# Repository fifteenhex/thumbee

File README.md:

This is dead. Look at https://github.com/fifteenhex/breadbee instead. It actually works. :D

# thumbee
MStar MSC313E SoC breakout

#rev0

Rough layout. Minimal decoupling caps because of limited space. Test to see if two layers works.
May move to some 0402 passives if not.

## bugs

Pinout foobar #1. USB ground isn't wired up because of a difference in the pin number of the symbol
and the footprint. Fixed by shorting the id pin to ground next to it.

Pinout foobar #2. avdd_nodie and dvdd_nodie are swapped. *edit* Maybe not. Seems like there is a datasheet
mistake. Pinout in the pin diagram is correct *edit* 

Pinout foobar #3. spi mosi and spi miso are swapped

Holtek USB->Serial chip is a piece of shit and can't handle lower baud rate data before data at the 
baud read the port was opened with.

1.8v supply is no good. The chip is very sensitive to the 1.8v rail dropping slightly (probably because
the DDR gets corrupted when it happens). On boot up the 1.8v drops for a split second and this makes
bootup hit or miss. Removing the 3.3va ldo and wiring 3.3va to 3.3v allows the input voltage to be lowered
to ~3.5v from the intended 5v and that makes the drop smaller.

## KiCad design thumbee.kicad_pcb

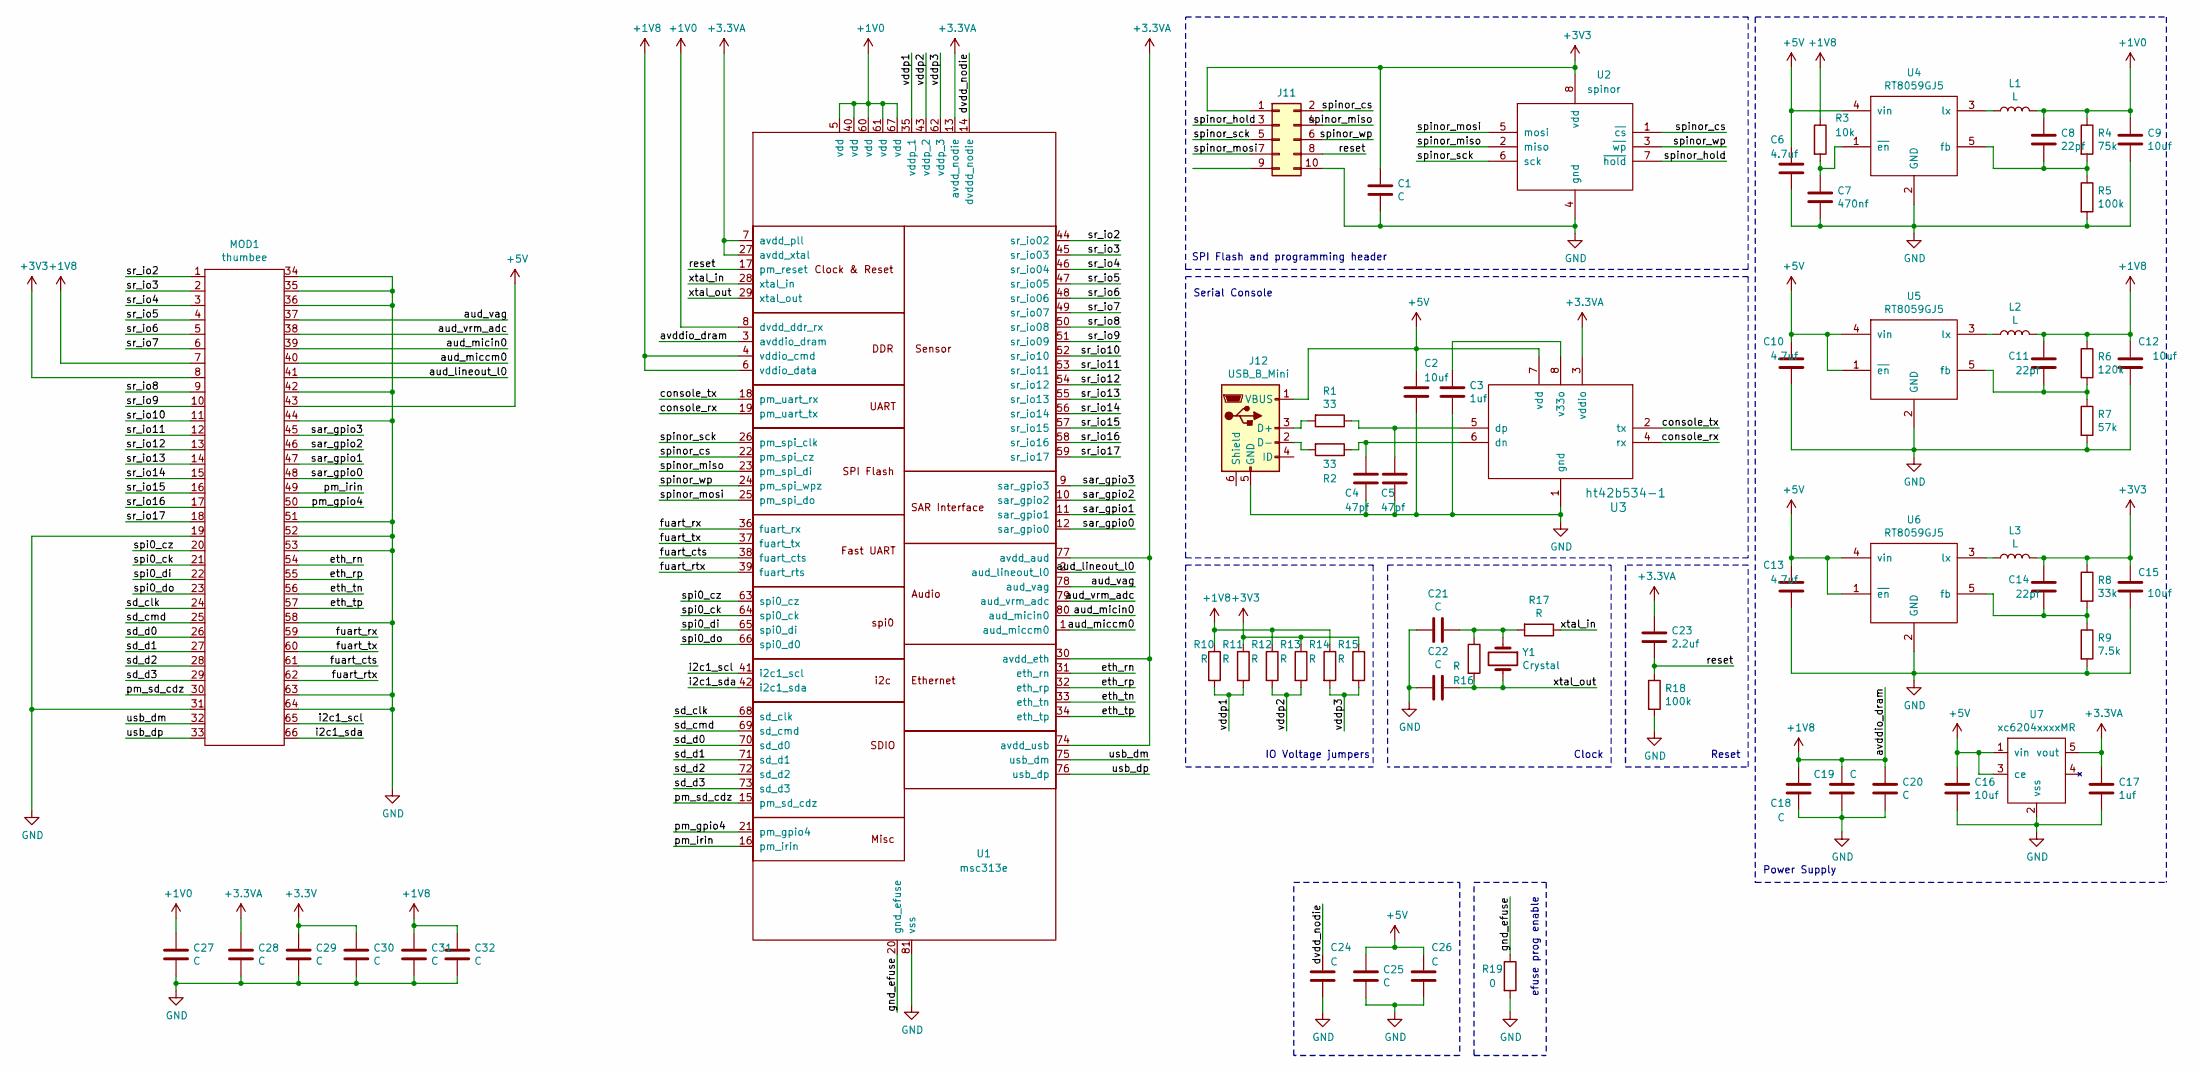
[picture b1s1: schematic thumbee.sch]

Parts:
C1, C18, C19, C20, C21, C22, C24, C25, C26, C27, C28, C29, C30, C31, C32: C; C_0603_1608Metric
C2, C9, C12, C15, C16: 10uf; C_0603_1608Metric
C3, C17: 1uf; C_0603_1608Metric
C4, C5: 47pf; C_0603_1608Metric
C6, C10, C13: 4.7uf; C_0603_1608Metric
C7: 470nf; C_0603_1608Metric
C8, C11, C14: 22pf; C_0603_1608Metric
C23: 2.2uf; C_0603_1608Metric
J11: Conn_02x05_Odd_Even; PinHeader_2x05_P1.00mm_Vertical_SMD
J12: USB_B_Mini; USB-MICRO-B
L1, L2, L3: L; CD32
MOD1: thumbee
R1, R2: 33; R_0603_1608Metric
R3: 10k; R_0603_1608Metric
R4: 75k; R_0603_1608Metric
R5, R18: 100k; R_0603_1608Metric
R6: 120k; R_0603_1608Metric
R7: 57k; R_0603_1608Metric
R8: 33k; R_0603_1608Metric
R9: 7.5k; R_0603_1608Metric
R10, R11, R12, R13, R14, R15, R16, R17: R; R_0603_1608Metric
R19: 0; R_0603_1608Metric
U1: msc313e; QFN-80_EP_8x8_Pitch0.35mm
U2: spinor; wson8-8x6mm
U3: ht42b534-1; SOIC-8_3.9x4.9mm_P1.27mm
U4, U5, U6: RT8059GJ5; TSOT-23-5
U7: xc6204xxxxMR; TSOT-23-5
Y1: Crystal; Crystal_SMD_5032-2Pin_5.0x3.2mm

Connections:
+1V0: C8.1, C9.1, C27.1, L1.2, R4.1, U1.5 (vdd), U1.8 (dvdd_ddr_rx), U1.40 (vdd), U1.60 (vdd), U1.61 (vdd), U1.67 (vdd)
+1V8: C11.1, C12.1, C18.1, C19.1, C20.1, C31.1, C32.1, L2.2, MOD1.7, R3.1, R6.1, R10.1, R12.1, R14.1, U1.3 (avddio_dram), U1.4 (vddio_cmd), U1.6 (vddio_data)
+3.3VA: C17.1, C23.1, C28.1, U1.7 (avdd_pll), U1.13 (avdd_nodie), U1.27 (avdd_xtal), U1.30 (avdd_eth), U1.74 (avdd_usb), U1.77 (avdd_aud), U3.3 (vddio), U7.5 (vout)
+5V: C2.1, C6.1, C10.1, C13.1, C16.1, C25.1, C26.1, J12.1 (VBUS), MOD1.43, U3.7 (vdd), U4.4 (vin), U5.1 (~en), U5.4 (vin), U6.1 (~en), U6.4 (vin), U7.1 (vin), U7.3 (ce)
/aud_lineout_l0: MOD1.41, U1.2 (aud_lineout_l0)
/aud_miccm0: MOD1.40, U1.1 (aud_miccm0)
/aud_micin0: MOD1.39, U1.80 (aud_micin0)
/aud_vag: MOD1.37, U1.78 (aud_vag)
/aud_vrm_adc: MOD1.38, U1.79 (aud_vrm_adc)
/console_rx: U1.19 (pm_uart_tx), U3.4 (rx)
/console_tx: U1.18 (pm_uart_rx), U3.2 (tx)
/dvdd_nodie: C24.2, U1.14 (dvddd_nodie)
/eth_rn: MOD1.54, U1.31 (eth_rn)
/eth_rp: MOD1.55, U1.32 (eth_rp)
/eth_tn: MOD1.56, U1.33 (eth_tn)
/eth_tp: MOD1.57, U1.34 (eth_tp)
/fuart_cts: MOD1.61, U1.38 (fuart_cts)
/fuart_rtx: MOD1.62, U1.39 (fuart_rts)
/fuart_rx: MOD1.59, U1.36 (fuart_rx)
/fuart_tx: MOD1.60, U1.37 (fuart_tx)
/gnd_efuse: R19.1, U1.20 (gnd_efuse)
/i2c1_scl: MOD1.65, U1.41 (i2c1_scl)
/i2c1_sda: MOD1.66, U1.42 (i2c1_sda)
/pm_gpio4: MOD1.50, U1.21 (pm_gpio4)
/pm_irin: MOD1.49, U1.16 (pm_irin)
/pm_sd_cdz: MOD1.30, U1.15 (pm_sd_cdz)
/reset: C23.2, J11.8, R18.1, U1.17 (pm_reset)
/sar_gpio0: MOD1.48, U1.12 (sar_gpio0)
/sar_gpio1: MOD1.47, U1.11 (sar_gpio1)
/sar_gpio2: MOD1.46, U1.10 (sar_gpio2)
/sar_gpio3: MOD1.45, U1.9 (sar_gpio3)
/sd_clk: MOD1.24, U1.68 (sd_clk)
/sd_cmd: MOD1.25, U1.69 (sd_cmd)
/sd_d0: MOD1.26, U1.70 (sd_d0)
/sd_d1: MOD1.27, U1.71 (sd_d1)
/sd_d2: MOD1.28, U1.72 (sd_d2)
/sd_d3: MOD1.29, U1.73 (sd_d3)
/spi0_ck: MOD1.21, U1.64 (spi0_ck)
/spi0_cz: MOD1.20, U1.63 (spi0_cz)
/spi0_di: MOD1.22, U1.65 (spi0_di)
/spi0_do: MOD1.23, U1.66 (spi0_d0)
/spinor_cs: J11.2, U1.22 (pm_spi_cz), U2.1 (~cs)
/spinor_hold: J11.3, U2.7 (~hold)
/spinor_miso: J11.4, U1.23 (pm_spi_di), U2.2 (miso)
/spinor_mosi: J11.7, U1.25 (pm_spi_do), U2.5 (mosi)
/spinor_sck: J11.5, U1.26 (pm_spi_clk), U2.6 (sck)
/spinor_wp: J11.6, U1.24 (pm_spi_wpz), U2.3 (~wp)
/sr_io2: MOD1.1, U1.44 (sr_io02)
/sr_io3: MOD1.2, U1.45 (sr_io03)
/sr_io4: MOD1.3, U1.46 (sr_io04)
/sr_io5: MOD1.4, U1.47 (sr_io05)
/sr_io6: MOD1.5, U1.48 (sr_io06)
/sr_io7: MOD1.6, U1.49 (sr_io07)
/sr_io8: MOD1.9, U1.50 (sr_io08)
/sr_io9: MOD1.10, U1.51 (sr_io09)
/sr_io10: MOD1.11, U1.52 (sr_io10)
/sr_io11: MOD1.12, U1.53 (sr_io11)
/sr_io12: MOD1.13, U1.54 (sr_io12)
/sr_io13: MOD1.14, U1.55 (sr_io13)
/sr_io14: MOD1.15, U1.56 (sr_io14)
/sr_io15: MOD1.16, U1.57 (sr_io15)
/sr_io16: MOD1.17, U1.58 (sr_io16)
/sr_io17: MOD1.18, U1.59 (sr_io17)
/usb_dm: MOD1.32, U1.75 (usb_dm)
/usb_dp: MOD1.33, U1.76 (usb_dp)
/vddp1: R10.2, R11.2, U1.35 (vddp_1)
/vddp2: R12.2, R13.2, U1.43 (vddp_2)
/vddp3: R14.2, R15.2, U1.62 (vddp_3)
/xtal_in: R17.1, U1.28 (xtal_in)
/xtal_out: C22.2, R16.2, U1.29 (xtal_out), Y1.2
GND: C1.2, C2.2, C3.2, C4.2, C5.2, C6.2, C7.2, C9.2, C10.2, C12.2, C13.2, C15.2, C16.2, C17.2, C18.2, C19.2, C20.2, C21.2, C22.1, C24.1, C25.2, C26.2, C27.2, C28.2, C29.2, C30.2, C31.2, C32.2, J11.10, J12.5 (GND), MOD1.19, MOD1.31, MOD1.34, MOD1.35, MOD1.36, MOD1.42, MOD1.44, MOD1.51, MOD1.52, MOD1.53, MOD1.58, MOD1.63, MOD1.64, R5.2, R7.2, R9.2, R18.2, R19.2, U1.81 (vss), U2.4 (gnd), U3.1 (gnd), U4.2 (GND), U5.2 (GND), U6.2 (GND), U7.2 (vss)
unnamed: C3.1, U3.8 (v33o)
unnamed: C4.1, R2.1, U3.6 (dn)
unnamed: C5.1, R1.1, U3.5 (dp)
unnamed: C7.1, R3.2, U4.1 (~en)
unnamed: C8.2, R4.2, R5.1, U4.5 (fb)
unnamed: C11.2, R6.2, R7.1, U5.5 (fb)
unnamed: C14.2, R8.2, R9.1, U6.5 (fb)
unnamed: C21.1, R16.1, R17.2, Y1.1
unnamed: J12.2 (D-), R2.2
unnamed: J12.3 (D+), R1.2
unnamed: L1.1, U4.3 (lx)
unnamed: L2.1, U5.3 (lx)
unnamed: L3.1, U6.3 (lx)

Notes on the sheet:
Power Supply
Reset
Serial Console
Clock
IO Voltage jumpers
efuse prog enable
SPI Flash and programming header

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
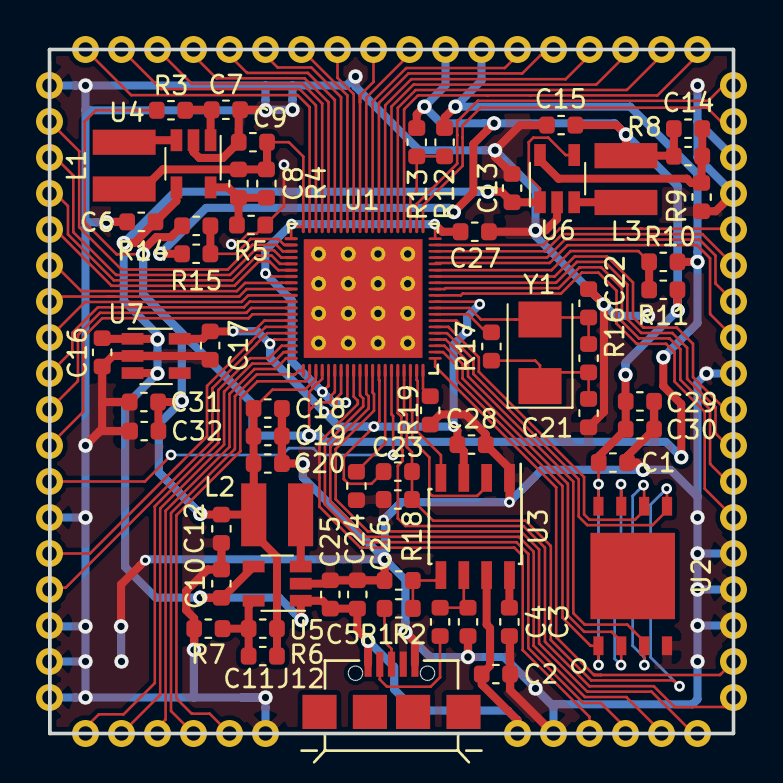
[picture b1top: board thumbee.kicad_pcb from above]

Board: 2 copper layers, 38.0 x 38.0 mm, 65 parts (1 on the bottom side), 85 nets.

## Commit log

2019-01-28 symbol and footprint
2019-02-05 Add remaining required components. Clean up schematic a bit.
2019-02-06 Almost complete schematic
2019-02-06 Fix schematic bugs. Assign footprints.
2019-02-08 QFN footprint fix up. Replace headers with a module footprint. Very rought parts layout and some routing.
2019-02-21 Rough all routed.
2019-02-22 Some clean up. Add some decoupling caps in the left over space.
2019-02-22 Rev0
2019-03-07 Document screwups so far
2019-03-10 Document more screw ups
2019-03-11 Fix msc313e symbol
2019-03-11 Add some component values. Fix avdd_nodie and dvdd_nodie.
2019-03-11 Re-route avdd_nodie and dvdd_nodie
2019-03-12 Fix USB pinout
2019-03-14 Moar bugs
2019-03-14 Fix pm spi pin swap. Revert dvdd_nodie and avdd_nodie.
2019-03-20 Update readme. Add photo of first working prototype
